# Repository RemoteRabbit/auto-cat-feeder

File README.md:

# Automatic Cat Feeder Project

An ESP32-S3 based automatic cat feeder: a stepper motor driven by a TMC2209 dispenses food on a schedule. The feeder is powered over USB-C Power Delivery.

<!-- TODO: photo or render of the feeder -->

## Status

Work in progress. The PCB schematic and layout are underway, the enclosure is being modeled in FreeCAD, and the firmware has not been started.

## Features

- USB-C PD power (15 V negotiated by a CH224A)
- TMC2209 stepper driver for quiet dispensing
- ESP32-S3 with Wi-Fi for scheduling and remote control
- TODO: feeding schedule, portion control, jam detection, notifications

## System overview

```
USB-C PD ──▶ CH224A ──▶ +15V ──┬──▶ TMC2209 ──▶ Stepper (dispenser)
                               └──▶ AP63205 buck ──▶ +5V ──▶ AMS1117 ──▶ +3V3 ──▶ ESP32-S3
```

## Repository layout

| Path        | Contents                                         |
|-------------|--------------------------------------------------|
| `pcb/`      | KiCad project for the control board              |
| `models/`   | FreeCAD models of the enclosure and mechanism    |
| `firmware/` | ESP32-S3 firmware                                |
| `docs/`     | Assembly, wiring, and hardware documentation     |

## License

TODO: choose licenses (for example CERN-OHL for hardware, MIT for firmware).

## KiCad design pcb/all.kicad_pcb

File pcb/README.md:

# Control Board (PCB)

Two-layer control board for the cat feeder, designed in **KiCad 10.0**.

Open `all.kicad_pro`. The top-level sheet is `all.kicad_sch`, and it has two sub-sheets:

- `power-delivery.kicad_sch`: USB-C PD input and the power rails
- `esp32-s3.kicad_sch`: microcontroller, stepper driver, and connectors

## Key parts

| Function         | Part               | Notes                                  |
|------------------|--------------------|----------------------------------------|
| MCU              | ESP32-S3-WROOM-1   | BOOT and RESET buttons on board        |
| Stepper driver   | TMC2209-LA         | 0.11 Ω sense resistors                 |
| USB-C PD sink    | CH224A             | Requests 15 V                          |
| 5 V buck         | AP63205WU          | 4.7 µH inductor                        |
| 3.3 V LDO        | AMS1117-3.3        |                                        |
| USB ESD          | USBLC6-2SC6        |                                        |
| Input protection | SMAJ18A TVS, 2 A polyfuse |                                 |

## Power rails

| Rail  | Source       | Used by       |
|-------|--------------|---------------|
| +15V  | USB-C PD     | TMC2209 motor supply (VS), AP63205 buck |
| +5V   | AP63205 buck | AMS1117 (powers the ESP32-S3), USBLC6 VBUS reference |
| +3V3  | AMS1117      | ESP32-S3, TMC2209 logic (VCC_IO), pull-ups |

TODO: current budget per rail.

## ESP32-S3 pinout

| GPIO   | Module pin | Net        | Connects to         | Notes |
|--------|-----------:|------------|---------------------|-------|
| EN     | 3          | ESP_EN     | RESET button (SW1)  | 10k pull-up to 3V3, 1 µF to GND |
| IO0    | 27         | ESP_BOOT   | BOOT button (SW2)   | Strapping pin; hold low at reset for download mode |
| IO4    | 4          | TMC_STEP   | TMC2209 STEP        | |
| IO5    | 5          | TMC_DIR    | TMC2209 DIR         | |
| IO6    | 6          | TMC_EN     | TMC2209 ~EN         | Active low; 10k pull-up keeps the driver off at boot |
| IO7    | 7          | TMC_DIAG   | TMC2209 DIAG        | StallGuard / fault output |
| IO8    | 12         | PD_PG      | CH224A PG           | Open-drain with 10k pull-up; CH224A pulls it low once PD negotiation succeeds |
| IO17   | 10         | TMC_TX     | TMC2209 PDN/UART    | UART TX through 1k (R9) |
| IO18   | 11         | TMC_UART   | TMC2209 PDN/UART    | UART RX, direct (single-wire UART) |
| IO19   | 13         | USB_DN     | USB-C D−            | Native USB, ESD-protected by USBLC6 |
| IO20   | 14         | USB_DP     | USB-C D+            | Native USB, ESD-protected by USBLC6 |

Unused: IO1–3, IO9–16, IO21, IO35–42, IO45–48, TXD0, RXD0. IO35–37 are taken by octal PSRAM on some WROOM-1 variants.

The TMC2209 has MS1 and MS2 tied to GND, so its UART address is 0.

The stepper connector (J2, JST 6-pin) uses pin 1 = A1, pin 3 = A2, pin 4 = B1, pin 6 = B2. Pins 2 and 5 are not connected.

## Bill of materials

Open `bom/ibom.html` in a browser for the interactive BOM. Regenerate it after board changes.

## Fabrication

Fabrication outputs are generated with the Fabrication Toolkit plugin, using the settings in `fabrication-toolkit-options.json`. Outputs are not committed.

TODO: fab house, stackup, thickness, finish, and assembly options.

## Revisions

| Rev  | Date | Changes | Known issues |
|------|------|---------|--------------|
| v0.1 | TODO | Initial design | TODO |

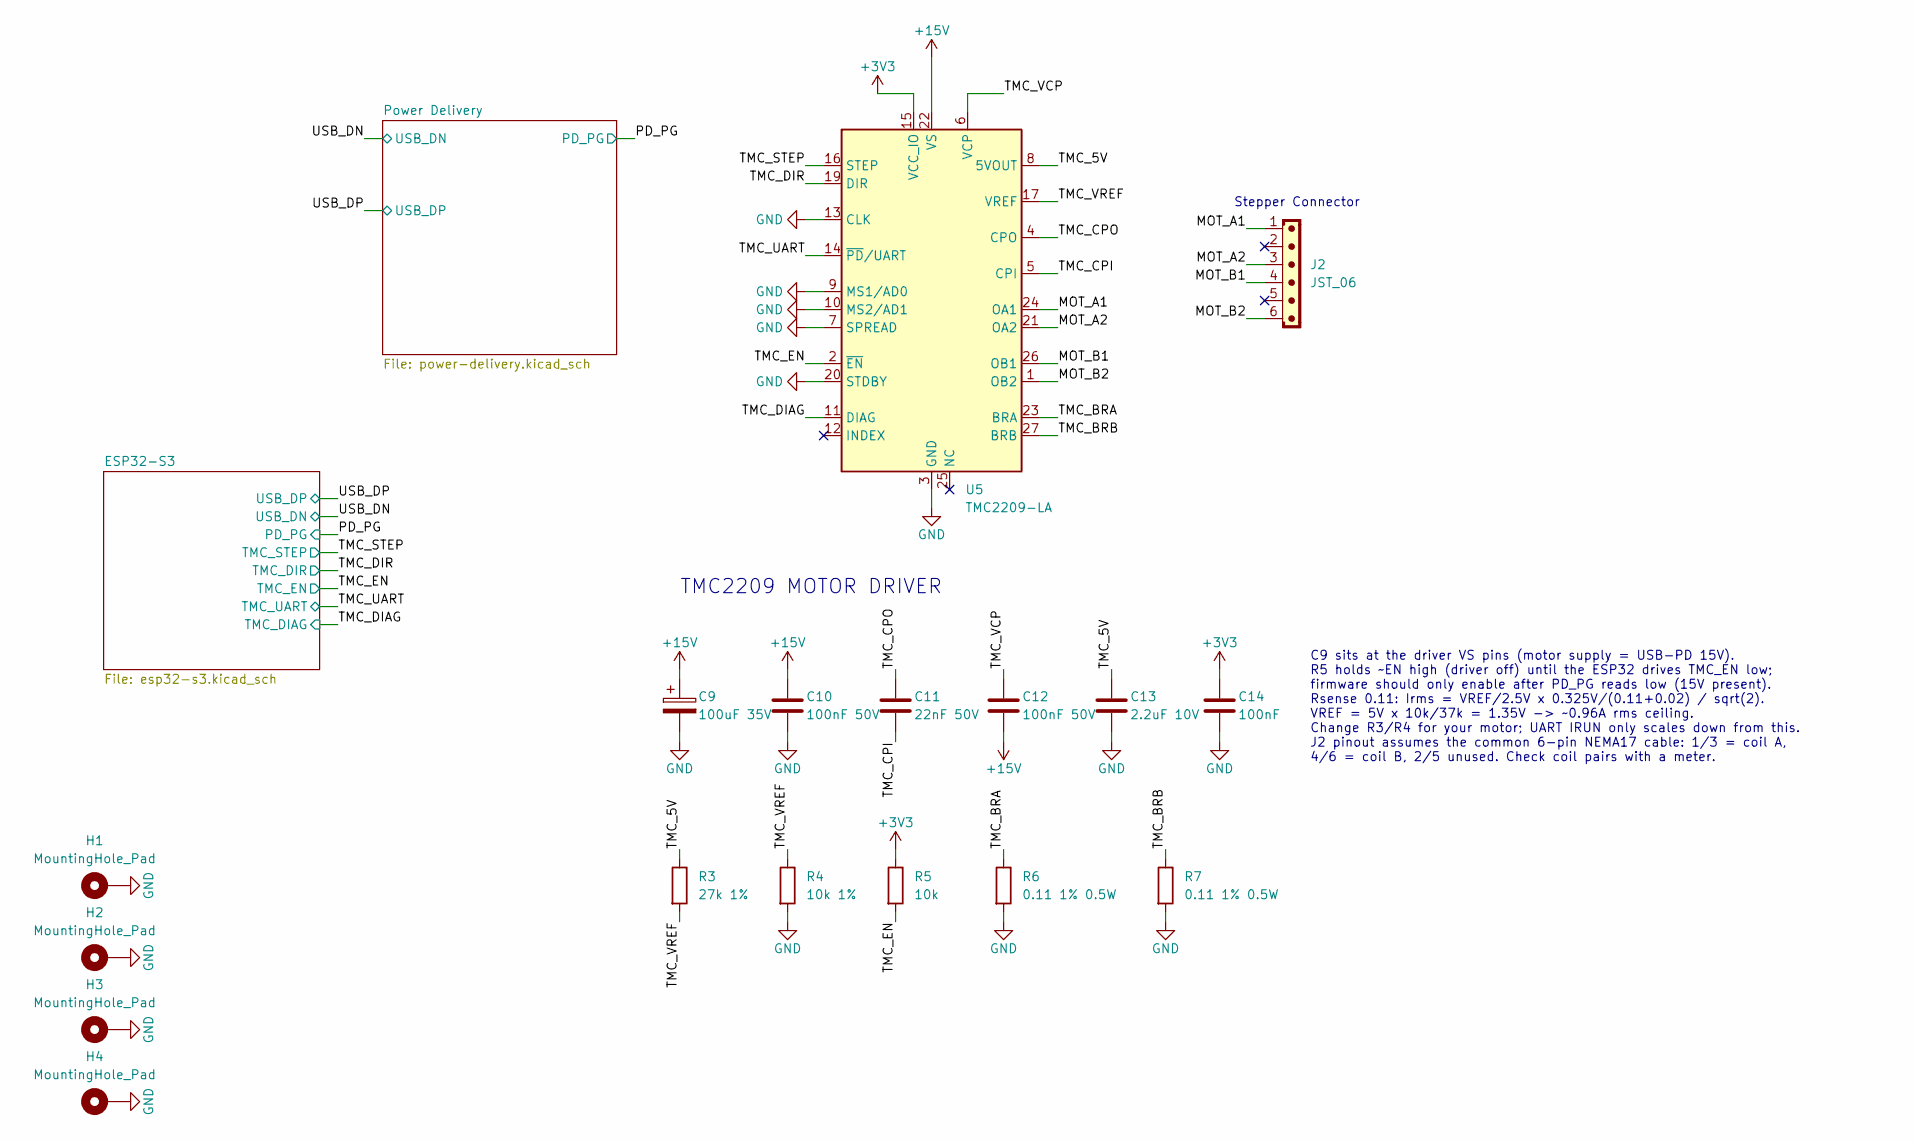
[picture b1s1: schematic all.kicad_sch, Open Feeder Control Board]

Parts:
C9: 100uF 35V; CP_Elec_8x10
C10, C12: 100nF 50V; C_0603_1608Metric
C11: 22nF 50V; C_0603_1608Metric
C13: 2.2uF 10V; C_0805_2012Metric
C14: 100nF; C_0603_1608Metric
H1, H2, H3, H4: MountingHole_Pad; MountingHole_3.2mm_M3_Pad_TopOnly
J2: JST_06; JST_EH_B6B-EH-A_1x06_P2.50mm_Vertical
R3: 27k 1%; R_0603_1608Metric
R4: 10k 1%; R_0603_1608Metric
R5: 10k; R_0603_1608Metric
R6, R7: 0.11 1% 0.5W; R_1206_3216Metric
U5: TMC2209-LA; VQFN-28-1EP_5x5mm_P0.5mm_EP3.7x3.7mm_ThermalVias

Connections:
+3V3: C14.1, R5.1, U5.15 (VCC_IO); also elsewhere on the board
+15V: C9.1, C10.1, C12.2, U5.22 (VS), U5.28 (VS); also elsewhere on the board
/MOT_A1: J2.1, U5.24 (OA1)
/MOT_A2: J2.3, U5.21 (OA2)
/MOT_B1: J2.4, U5.26 (OB1)
/MOT_B2: J2.6, U5.1 (OB2)
/TMC_5V: C13.1, R3.1, U5.8 (5VOUT)
/TMC_BRA: R6.1, U5.23 (BRA)
/TMC_BRB: R7.1, U5.27 (BRB)
/TMC_CPI: C11.2, U5.5 (CPI)
/TMC_CPO: C11.1, U5.4 (CPO)
/TMC_DIAG: U5.11 (DIAG); also elsewhere on the board
/TMC_DIR: U5.19 (DIR); also elsewhere on the board
/TMC_EN: R5.2, U5.2 (~EN); also elsewhere on the board
/TMC_STEP: U5.16 (STEP); also elsewhere on the board
/TMC_UART: U5.14 (~PD/UART); also elsewhere on the board
/TMC_VCP: C12.1, U5.6 (VCP)
/TMC_VREF: R3.2, R4.1, U5.17 (VREF)
GND: C9.2, C10.2, C13.2, C14.2, H1.1 (1_1), H2.1 (1_1), H3.1 (1_1), H4.1 (1_1), R4.2, R6.2, R7.2, U5.3 (GND), U5.7 (SPREAD), U5.9 (MS1/AD0), U5.10 (MS2/AD1), U5.13 (CLK), U5.18 (GND), U5.20 (STDBY), U5.29 (GND); also elsewhere on the board

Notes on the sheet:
TMC2209 MOTOR DRIVER
C9 sits at the driver VS pins (motor supply = USB-PD 15V). R5 holds ~EN high (driver off) until the ESP32 drives TMC_EN low; firmware should only enable after PD_PG reads low (15V present). Rsense 0.11: Irms = VREF/2.5V x 0.325V/(0.11+0.02) / sqrt(2). VREF = 5V x 10k/37k = 1.35V -> ~0.96A rms ceili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
Stepper Connector

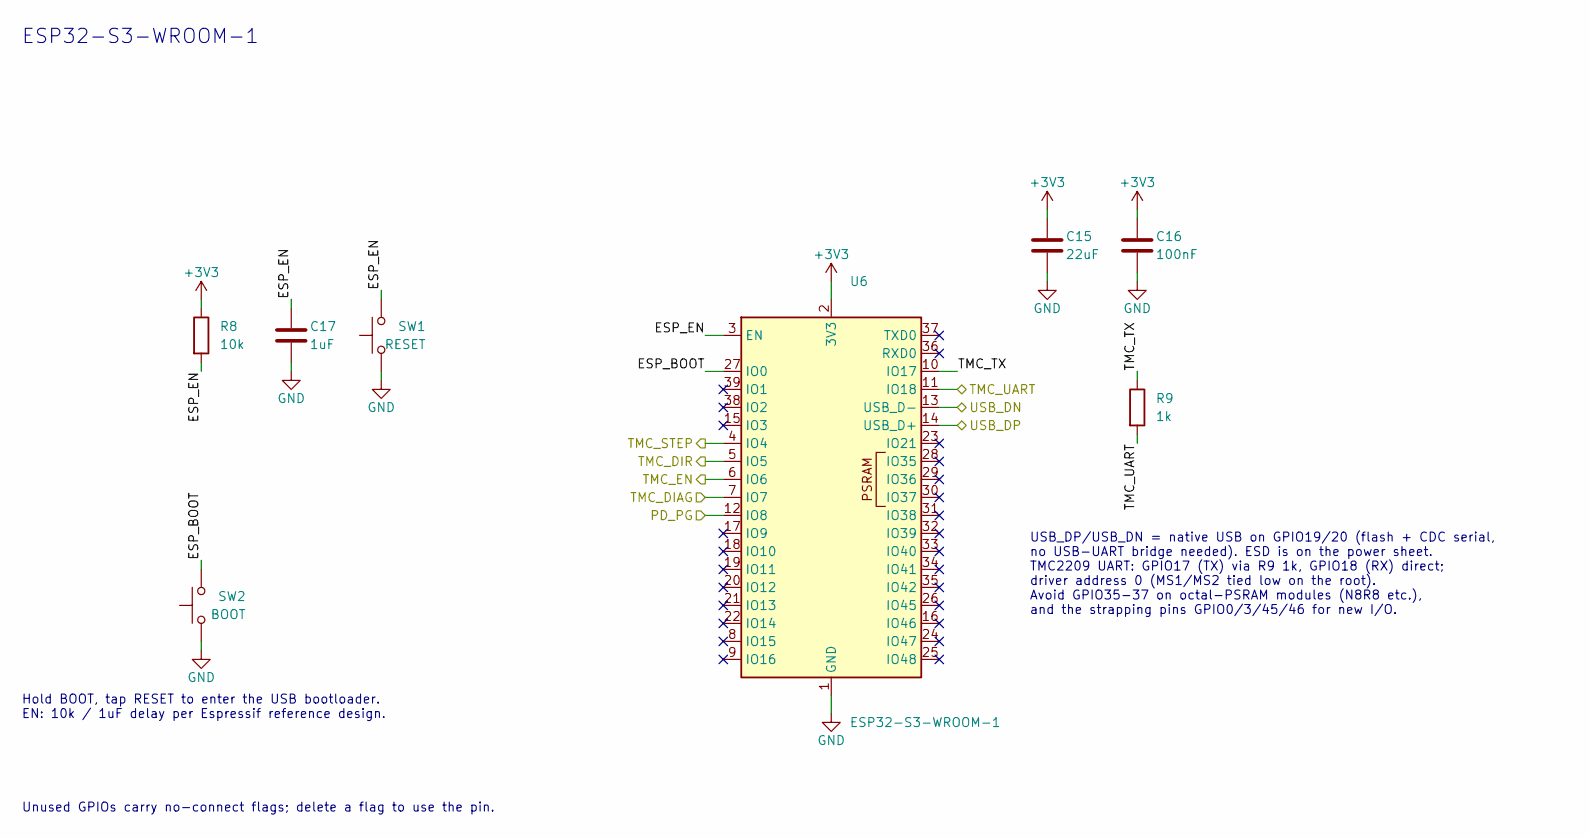
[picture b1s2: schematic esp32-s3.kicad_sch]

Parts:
C15: 22uF; C_0805_2012Metric
C16: 100nF; C_0603_1608Metric
C17: 1uF; C_0603_1608Metric
R8: 10k; R_0603_1608Metric
R9: 1k; R_0603_1608Metric
SW1: RESET; SW_SPST_TL3342
SW2: BOOT; SW_SPST_TL3342
U6: ESP32-S3-WROOM-1

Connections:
+3V3: C15.1, C16.1, R8.1, U6.2 (3V3); also elsewhere on the board
/ESP32-S3/ESP_BOOT: SW2.2, U6.27 (IO0)
/ESP32-S3/ESP_EN: C17.1, R8.2, SW1.2, U6.3 (EN)
/ESP32-S3/TMC_TX: R9.1, U6.10 (IO17)
/PD_PG: U6.12 (IO8); also elsewhere on the board
/TMC_DIAG: U6.7 (IO7); also elsewhere on the board
/TMC_DIR: U6.5 (IO5); also elsewhere on the board
/TMC_EN: U6.6 (IO6); also elsewhere on the board
/TMC_STEP: U6.4 (IO4); also elsewhere on the board
/TMC_UART: R9.2, U6.11 (IO18); also elsewhere on the board
/USB_DN: U6.13 (USB_D-); also elsewhere on the board
/USB_DP: U6.14 (USB_D+); also elsewhere on the board
GND: C15.2, C16.2, C17.2, SW1.1, SW2.1, U6.1 (GND), U6.40 (GND), U6.41 (GND); also elsewhere on the board

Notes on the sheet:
USB_DP/USB_DN = native USB on GPIO19/20 (flash + CDC serial, no USB-UART bridge needed). ESD is on the power sheet. TMC2209 UART: GPIO17 (TX) via R9 1k, GPIO18 (RX) direct; driver address 0 (MS1/MS2 tied low on the root). Avoid GPIO35-37 on octal-PSRAM modules (N8R8 etc.), and the strapping pins GP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
ESP32-S3-WROOM-1
Hold BOOT, tap RESET to enter the USB bootloader. EN: 10k / 1uF delay per Espressif reference design.
Unused GPIOs carry no-connect flags; delete a flag to use the pin.

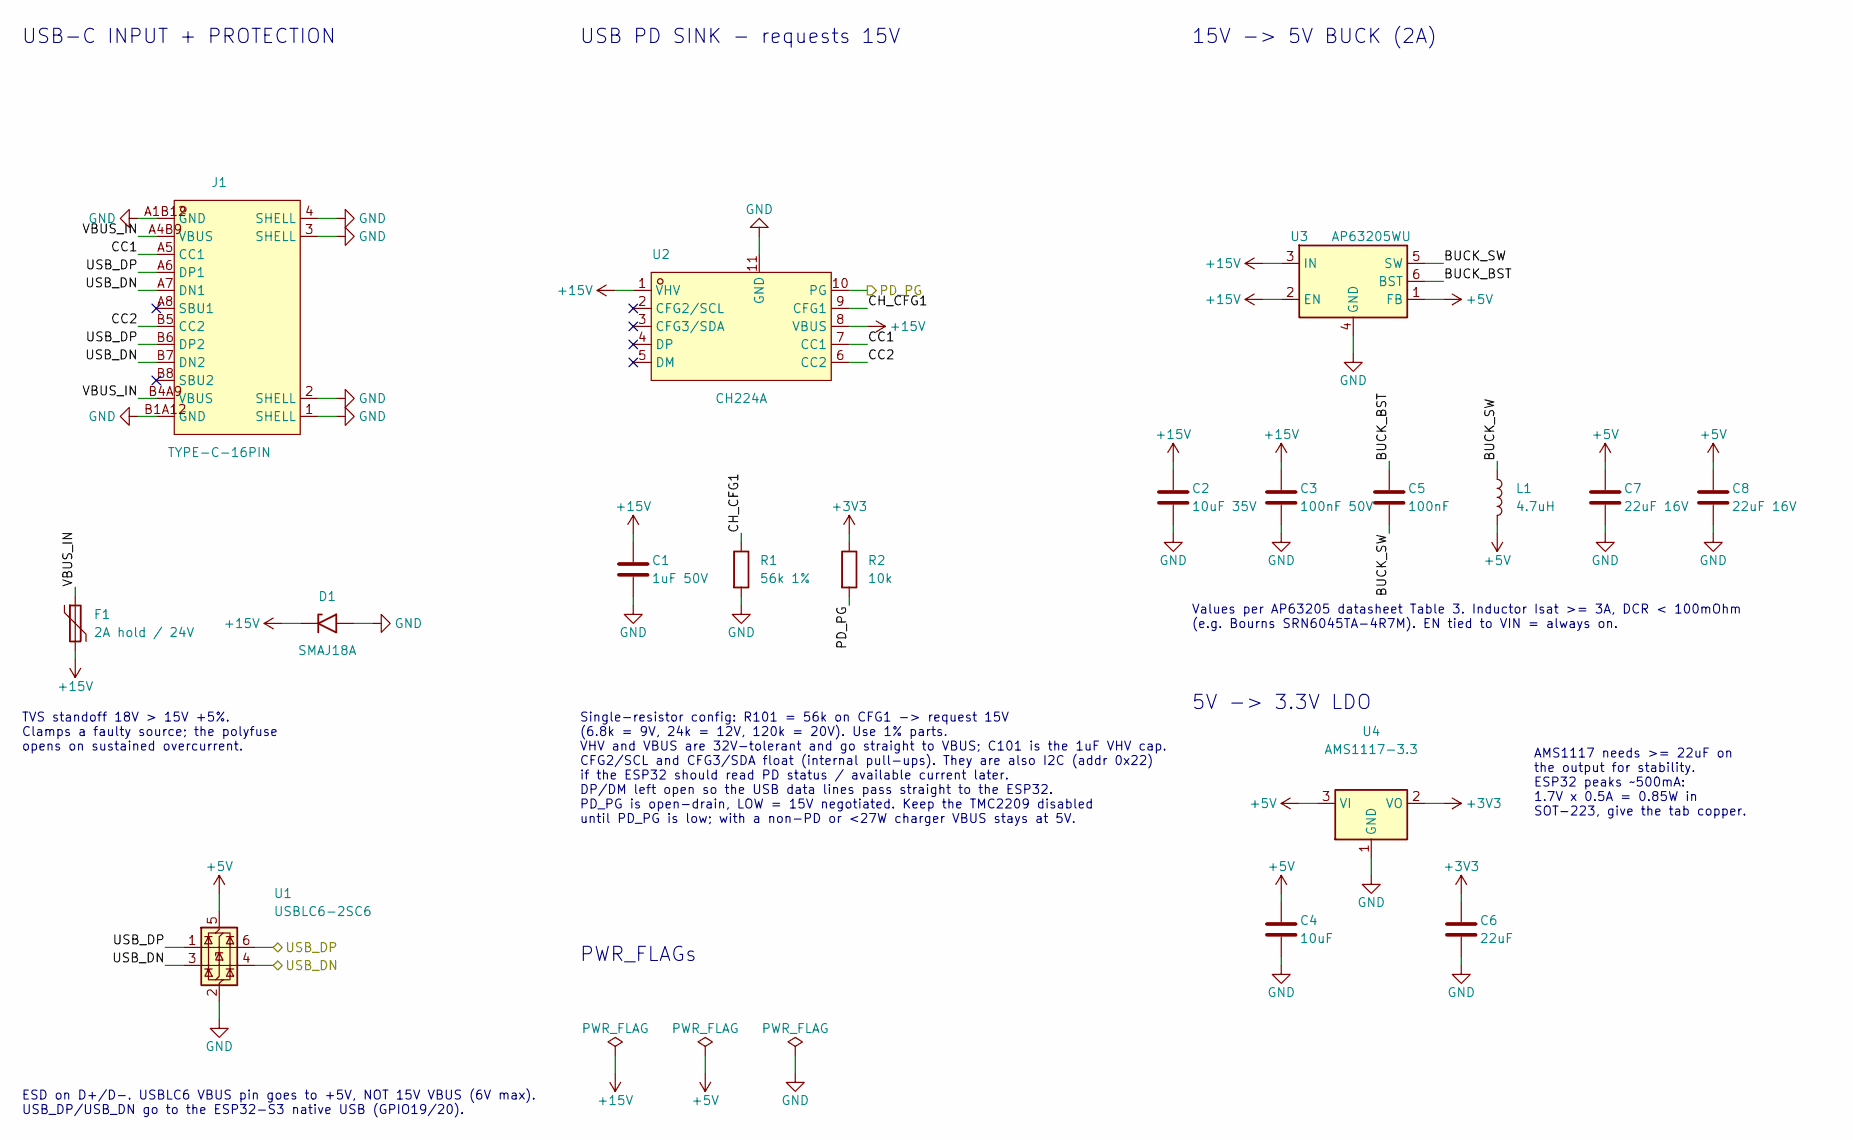
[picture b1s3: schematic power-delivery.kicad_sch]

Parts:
C1: 1uF 50V; C_0805_2012Metric
C2: 10uF 35V; C_1206_3216Metric
C3: 100nF 50V; C_0603_1608Metric
C4: 10uF; C_0805_2012Metric
C5: 100nF; C_0603_1608Metric
C6: 22uF; C_0805_2012Metric
C7, C8: 22uF 16V; C_1206_3216Metric
D1: SMAJ18A; D_SMA
F1: 2A hold / 24V; Fuse_1812_4532Metric
J1: TYPE-C-16PIN; USB-C-SMD_TYPE-C16PIN-SHOUHAN; LCSC Part C53207801
L1: 4.7uH; L_Bourns_SRN6045TA
R1: 56k 1%; R_0603_1608Metric
R2: 10k; R_0603_1608Metric
U1: USBLC6-2SC6; SOT-23-6
U2: CH224A; ESSOP-10_L4.9-W3.9-P1.0-LS6.0-TL-EP; LCSC Part C42459160
U3: AP63205WU; TSOT-23-6
U4: AMS1117-3.3; SOT-223-3_TabPin2

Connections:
+3V3: C6.1, R2.1, U4.2 (VO); also elsewhere on the board
+5V: C4.1, C7.1, C8.1, L1.2, U1.5 (VBUS), U3.1 (FB), U4.3 (VI)
+15V: C1.1, C2.1, C3.1, D1.1 (A1), F1.2, U2.1 (VHV), U2.8 (VBUS), U3.2 (EN), U3.3 (IN); also elsewhere on the board
/PD_PG: R2.2, U2.10 (PG); also elsewhere on the board
/Power Delivery/BUCK_BST: C5.1, U3.6 (BST)
/Power Delivery/BUCK_SW: C5.2, L1.1, U3.5 (SW)
/Power Delivery/CC1: J1.A5 (CC1), U2.7 (CC1)
/Power Delivery/CC2: J1.B5 (CC2), U2.6 (CC2)
/Power Delivery/CH_CFG1: R1.1, U2.9 (CFG1)
/Power Delivery/VBUS_IN: F1.1, J1.A4B9 (VBUS), J1.B4A9 (VBUS)
/USB_DN: J1.A7 (DN1), J1.B7 (DN2), U1.3 (I/O2), U1.4 (I/O2); also elsewhere on the board
/USB_DP: J1.A6 (DP1), J1.B6 (DP2), U1.1 (I/O1), U1.6 (I/O1); also elsewhere on the board
GND: C1.2, C2.2, C3.2, C4.2, C6.2, C7.2, C8.2, D1.2 (A2), J1.1 (SHELL), J1.2 (SHELL), J1.3 (SHELL), J1.4 (SHELL), J1.A1B12 (GND), J1.B1A12 (GND), R1.2, U1.2 (GND), U2.11 (GND), U3.4 (GND), U4.1 (GND); also elsewhere on the board

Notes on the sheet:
PWR_FLAGs
15V -> 5V BUCK (2A)
TVS standoff 18V > 15V +5%. Clamps a faulty source; the polyfuse opens on sustained overcurrent.
ESD on D+/D-. USBLC6 VBUS pin goes to +5V, NOT 15V VBUS (6V max). USB_DP/USB_DN go to the ESP32-S3 native USB (GPIO19/20).
Values per AP63205 datasheet Table 3. Inductor Isat >= 3A, DCR < 100mOhm (e.g. Bourns SRN6045TA-4R7M). EN tied to VIN = always on.
Single-resistor config: R101 = 56k on CFG1 -> request 15V (6.8k = 9V, 24k = 12V, 120k = 20V). Use 1% parts. VHV and VBUS are 32V-tolerant and go straight to VBUS; C101 is the 1uF VHV cap. CFG2/SCL and CFG3/SDA float (internal pull-ups). They are also I2C (addr 0x22) if the ESP32 should read PD stat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
USB PD SINK - requests 15V
5V -> 3.3V LDO
USB-C INPUT + PROTECTION
AMS1117 needs >= 22uF on the output for stability. ESP32 peaks ~500mA: 1.7V x 0.5A = 0.85W in SOT-223, give the tab copper.

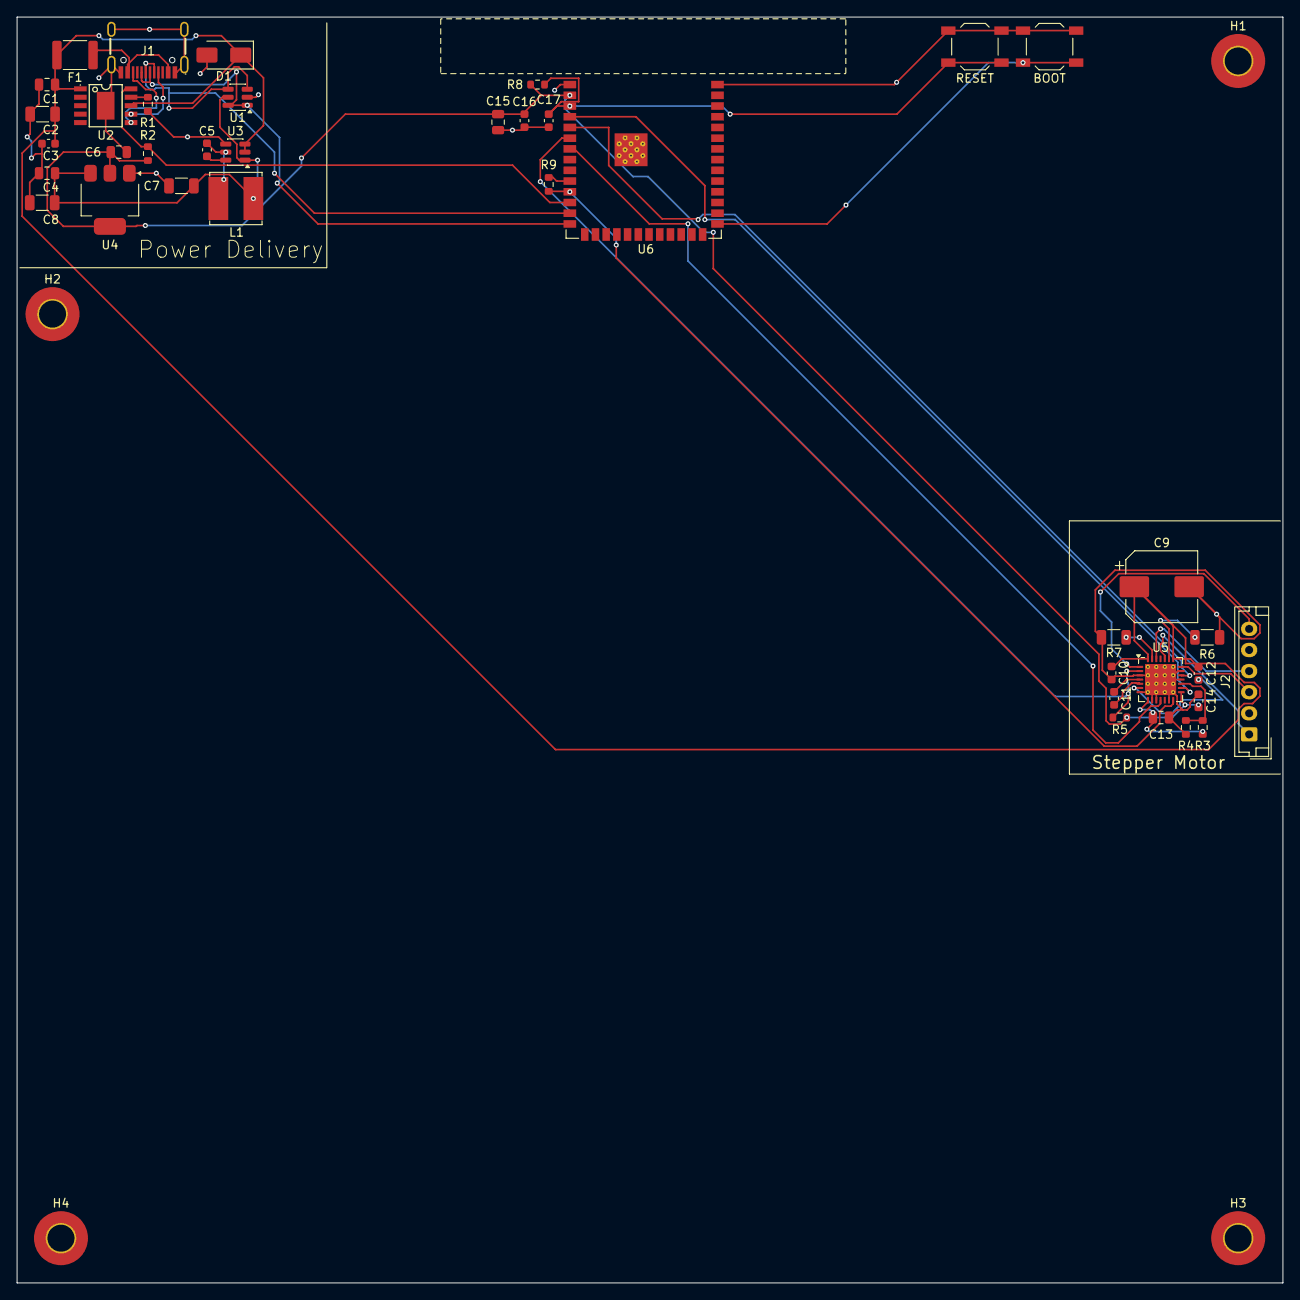
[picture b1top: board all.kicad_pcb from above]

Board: 2 copper layers, 150.0 x 150.0 mm, 43 parts (0 on the bottom side), 32 nets.
